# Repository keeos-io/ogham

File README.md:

# Ogham

A dual-voice **bytebeat synthesizer** for Eurorack, built on the Electro-Smith
Daisy Seed. This repository holds everything needed to build one: firmware
source, schematics, PCB, panel, and the fabrication package.

Instead of oscillators and wavetables, Ogham runs *bytebeat* expressions —
single lines of integer arithmetic that, evaluated over time, produce
surprisingly rich rhythmic and melodic patterns. It hosts a bank of them, plays
two at once, and clocks, pitches and modulates them from the rest of your rack.

- **Manual:** <https://keeos.io/docs/ogham-manual/> (or [`docs/ogham-manual.pdf`](docs/ogham-manual.pdf))
- **Firmware downloads and changelog:** <https://keeos.io/firmware/ogham/>
- **Module overview:** <https://keeos.io/modules/ogham/>

> **Status: prototype.** Built and tested on a handful of units, not qualified
> for production. Published so others can learn from it and build on it. Check
> the design yourself before you commit money to a fab run.

## What's here

| Path | Contents |
|---|---|
| [`firmware/`](firmware/) | Firmware source, build and flashing instructions |
| [`hardware/ogham-merged-v1.0/`](hardware/ogham-merged-v1.0/) | KiCad schematics and PCB — the shipping revision |
| [`hardware/panel/`](hardware/panel/) | Front panel: artwork, and the panel PCB project |
| [`hardware/production/`](hardware/production/) | Gerbers, BOM, placement — ready to upload to a fab |
| [`docs/`](docs/) | Build instructions, and the manual as a PDF |
| `lib/` | libDaisy and DaisySP, as pinned submodules |

Only the **current** board revision is published. Earlier prototypes are not
included, so there is nothing here to fabricate by mistake.

## Quick start

**To build the firmware** — [`docs/BUILDING.md`](docs/BUILDING.md) has the full
set-up for Windows, macOS and Linux; [`firmware/README.md`](firmware/README.md)
covers the firmware itself. In short:

```bash
git clone --recurse-submodules https://github.com/keeos-io/ogham.git
cd ogham && make -C lib/libDaisy -j8 && make -C lib/DaisySP -j8
cd firmware && make -j8
```

`--recurse-submodules` is not optional: libDaisy has nested submodules of its
own, and without them the build fails part-way with a missing HAL object.

**To have the boards made** — see [`hardware/README.md`](hardware/README.md).
Upload `hardware/production/ogham-merged-v1.0.zip`, and **read the
hand-populate list first**: several parts are deliberately excluded from
assembly and a board built from the BOM alone will be missing them.

## Licensing

Firmware is **MIT**. Hardware and documentation are **CC BY-SA 4.0**. Build one,
sell one, fork it — but share hardware modifications alike, and give credit. The
*Keeos* name and the panel identity are not covered.

Full terms in [`LICENSE.md`](LICENSE.md); third-party components and the panel
typefaces in [`THIRD-PARTY.md`](THIRD-PARTY.md).

## A note on reproducible builds

The published binaries are byte-for-byte reproducible from this repository.
Building the firmware at a given tag, with the submodules at their pinned
commits and **Arm GNU Toolchain 14.2.Rel1**, reproduces the exact `.bin` shipped
for that release — verified, not assumed.

Two things will break that: building against a *different* libDaisy commit, or a
different compiler version. Both produce working firmware; neither reproduces the
published checksums. If you are verifying a download rather than developing,
compare against the SHA-256 published with each release.

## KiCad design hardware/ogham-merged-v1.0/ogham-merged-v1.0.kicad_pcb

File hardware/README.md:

# Ogham hardware

KiCad 10 sources and a ready-to-upload fabrication package for the shipping
board revision, **ogham-merged-v1.0**.

| | |
|---|---|
| Main PCB | 50 × 110 mm, 2-layer, double-sided SMT |
| Panel | 10 HP (50.5 × 128.5 mm) |
| Depth behind panel | ~32 mm including power-cable clearance — skiff-friendly |
| Supply | Eurorack ±12 V; the Seed runs from +12 V through a series Schottky, and an on-board +5 V regulator feeds the display and logic |
| MCU | Electro-Smith Daisy Seed (STM32H750), on pin-header standoffs |

Only this revision is published. Earlier prototypes (`ogham-logic`, `ogham-ui`
and their v0.2 iterations) are not included, so there is nothing here to
fabricate by mistake.

## Layout

| Path | Contents |
|---|---|
| `ogham-merged-v1.0/` | Schematics (hierarchical: power, MCU, CV I/O, audio, UI), PCB, netlist |
| `panel/` | Panel artwork as SVG, and the panel as a fabricable PCB (`PanelPCB-v2/`) |
| `production/` | Gerbers, BOM, placement, IPC netlist, and the interactive BOM |

The schematic is a two-level hierarchy: `ogham-merged-v1.0` is the root, and it
pulls in `ogham-logic-v2.0` (→ power, MCU, CV I/O) and `ogham-ui-v0.2` (→ audio,
UI). Those two keep the sheet names they had when the design was two separate
boards — they are **not** old revisions, they are live sub-sheets of this one.

## 3D models are not included

The PCB references five third-party 3D models. They are other people's files, in
one case 34 MB of one, and several arrived without a licence attached, so they
are not redistributed here. Everything else the board needs is in this
repository; only the 3D viewer is affected, and the board fabricates,
assembles and works without them.

The references are `${KIPRJMOD}`-relative, which means KiCad resolves them
against the project directory. Create `hardware/_libs/` and drop the files in
at these paths and the 3D view fills in with no edit to the PCB:

| Path under `hardware/_libs/` | Part | Source | Licence |
|---|---|---|---|
| `AudioJacks/AudioJacks.3dshapes/PJ398SM_Hex_nut.step` | Thonkiconn PJ398SM jacks | [clacktronics/AudioJacks](https://github.com/clacktronics/AudioJacks) | MIT |
| `kicad-3dmodels/potentiometers/ALPHA-RD901F-40.step` | Alpha 9mm pots | [dhaillant/kicad-3dmodels](https://github.com/dhaillant/kicad-3dmodels) | GPL-3.0 |
| `TM1637/YAAJ_4_Digit_LED_Display_0_36_Dots_TM1637_PinHeader_Left_cp.step` | TM1637 display | [yet-another-average-joe/KiCad-Chinese_Modules](https://github.com/yet-another-average-joe/KiCad-Chinese_Modules) | not stated upstream |
| `DaisySeed/ES_Daisy_Seed_Rev7-1.step` | Daisy Seed | Electro-Smith | not stated on the copy used here |
| `Encoder/EC11E1834403/3D/EC11E1834403.stp` | EC11 encoder | manufacturer model; provenance not recorded | unknown |
| `vendor/2MS1T1B1M2QES--3DModel-STEP-56544.STEP` | Mode toggle switch | manufacturer model | unknown |
| `vendor/TAP106J016SCS.STEP` | Tantalum capacitor | manufacturer model | unknown |

A missing model is a warning, not an error: KiCad opens the board and reports
which ones it could not find. Note also that each jack footprint carries a
second, dead model entry naming `${KICAD9_3DMODEL_DIR}`, a KiCad 9 path
variable that KiCad 10 does not define. The jacks render from the AudioJacks
model above, so that entry can be ignored.

## Browse the design without installing anything

[KiCanvas](https://kicanvas.org) renders KiCad files in the browser, straight
from this repository — pan, zoom, click a symbol, follow a net. Nothing to
install, nothing to download.

| | |
|---|---|
| Schematic and PCB | [Open in KiCanvas](https://kicanvas.org/?github=https://github.com/keeos-io/ogham/tree/main/hardware/ogham-merged-v1.0) |
| Panel PCB | [Open in KiCanvas](https://kicanvas.org/?github=https://github.com/keeos-io/ogham/tree/main/hardware/panel/PanelPCB-v2) |

Both links point at a **directory**, not at a file, and that is deliberate. Given
a single `.kicad_sch` KiCanvas loads it alone, which for a hierarchical design
means the root sheet and nothing below it — you would get a page of sheet symbols
with no way into them. Pointed at the directory it enumerates every file, so all
nine sheets resolve and the board is in the same viewer, behind the file picker
at the top left.

This matters more than convenience: these are **KiCad 10** sources, and KiCad 9
cannot open them at all. Until you have KiCad 10 in front of you, the links above
are the only way to read the circuit.

KiCanvas is a third-party viewer and fetches from GitHub anonymously, so it is
subject to GitHub's rate limits and is nobody's idea of a permanent archive. The
files in this repository are the source of truth; the links are a convenience.

## Having the boards made

The package in `production/` is formatted for JLCPCB assembly, but the gerbers
are standard and will work anywhere. **Read
[`production/JLC-upload-checklist.md`](production/JLC-upload-checklist.md)
before ordering** — it covers the whole flow, including the two things most
likely to cost you a board run.

### ⚠ 1. Nineteen parts must be marked "Do Not Place"

90 SMD parts are machine-assembled. **19 designators across 13 BOM rows are
hand-soldered** and will be flagged by the fab as unresolvable, because they
carry no LCSC number. Mark every one of them DNP:

- **C5** — 10 µF tantalum (`TAP106J016SCS`). This one is easy to miss: it looks
  like an ordinary SMD part in the BOM and it is the **+5 V bulk capacitor**, so
  a board that quietly ships without it is not a board you want.
- **A1** — the Daisy Seed
- **J1** — Eurorack power header
- **8 × jacks** — `J_CLK1`, `J_CVA1`, `J_CVB1`, `J_GATE_IN1`, `J_CV_OUT1`,
  `J_GATE_OUT1`, `J_OUT1`, `J_OUT2`
- **J_DISP1**, **J_DISP_SUPP** — display headers
- **4 × pots** — `RVA1`, `RVB1`, `RVLEVEL1`, `RVRATE1`
- **SW_ENC1** — encoder · **SW_MODE1** — mode toggle

### ⚠ 2. Check rotations before you confirm

Rotation is the classic assembly error — KiCad and the fab disagree about
reference orientation. Step through the placement preview and check the
polarised parts: diode cathodes (D1, D2, D8, D3, D4, D5, D_OCT1, D_OCT2, D6,
D7), IC pin-1 (U1–U7), and Q1's collector/emitter. Assembly is **double-sided**,
so also confirm the top-layer parts really are on top.

## Interactive BOM — use this while assembling

[`production/ogham-merged-v1.0-ibom.html`](production/ogham-merged-v1.0-ibom.html)
is a single self-contained file: click a line in the BOM and those parts light up
on the board, front and back, with checkboxes for tracking what you have sourced
and placed. No install, no network — **download it and open it in a browser**.

> GitHub displays committed HTML as source rather than rendering it, so use the
> download button rather than clicking through — the file is useless as text and
> perfectly good once saved.

It carries an **LCSC** column, which doubles as the hand-populate list: a part
with an LCSC number is machine-assembled, and a part **without** one is yours to
solder. `C5` shows its bare MPN `TAP106J016SCS`, and the jacks, pots, encoder and
headers show nothing at all — those are exactly the 19 designators to mark Do Not
Place.

Regenerate it with [`gen-ibom.sh`](gen-ibom.sh) whenever the board changes; the
output is committed, so it can otherwise drift from the design. It needs KiCad's
own Python and [InteractiveHtmlBom](https://github.com/openscopeproject/InteractiveHtmlBom)
**v2.11.2 or newer** — earlier versions cannot read KiCad 10 files.

## Hand-populated parts

Sources that have worked (UK):

| Part | Qty | Where |
|---|---|---|
| Thonkiconn PJ398SM jacks | 8 | [thonk.co.uk](https://www.thonk.co.uk/shop/thonkiconn/) |
| Alpha 9 mm B10K D-shaft pots | 4 | [thonk.co.uk](https://www.thonk.co.uk/shop/alpha-9mm-pots-dshaft/) |
| Rotary encoder, Bourns `PEC11R-4115K-S0018` | 1 | Any distributor — Mouser, Farnell, Digi-Key |
| Breakaway pin header | 1 bag | [thonk.co.uk](https://www.thonk.co.uk/shop/60-pin-header/) |
| 2×5 IDC power header | 1 | Mouser / Soundtronics / York Modular |
| Daisy Seed (Rev 4) | 1 | Electro-Smith |
| C5, 10 µF tantalum | 1 | Any distributor — `TAP106J016SCS` or equivalent |

> **Encoder note.** `PEC11R-4115K-S0018` is a 15 mm knurled (T18) shaft with a
> push switch, 18 detents and 18 pulses per revolution — one pulse per detent.
> It is the swapped-A/B part, which the **default** firmware build targets. Two
> batches exist with opposite A/B phase and the firmware cannot tell them apart,
> so if the Func encoder counts down when turned clockwise, flash the other
> build — see [`../firmware/README.md`](../firmware/README.md).
>
> **Why the 15 mm shaft.** It matches the Alpha pots dimensionally: the same
> 5 mm M7 × 0.75 bushing and the same 15 mm from mounting shoulder to shaft tip,
> so the encoder knob sits level with the four pot knobs rather than standing
> proud of them. The 20 mm variant of the same encoder carries a 7 mm bushing
> and would not. The cost of that choice is a short thread — 5 mm of bushing
> against a 1.6 mm panel — so expect to pack a washer under the nut to pull the
> encoder flush.

## Panel

`panel/` holds the artwork as SVG and as a fabricable PCB, which is how the
panels were actually made — a PCB panel is cheap, flat, and takes the graphics as
silkscreen.

`Ogham Panel Graphics (JLCPCB) v2.svg` is the editable artwork, and
`PanelPCB-v2/` is the KiCad project converted from it — that project, and the
gerbers in its `production/`, are what the built modules use. The first
revision has been removed to leave only one panel to order from; it is still in
the git history if you want it.

**The fabrication files do not depend on any fonts.** The artwork is stored as
polygons, converted from the SVG, so a panel ordered from
`PanelPCB-v2/production/` comes out right regardless of what is installed on your
machine.

**Editing the SVG does need fonts**, though all three are now free and
redistributable — the v2 artwork replaced Bahnschrift, a Windows system font,
with DINish. See
[`../THIRD-PARTY.md`](../THIRD-PARTY.md) for the full list and what to do on
macOS or Linux.

## Design notes

`ogham_pins.h` in the firmware is the pin-assignment source of truth and matches
this schematic. If you rework the board, keep them in step.

Two constraints worth knowing before you move things: the TM1637 display sits on
**D9/D10 (PB4/PB5)**, which are SPI pins with **no I²C alternate function** — an
I²C peripheral needs different pins. Seed pins 12/13 (PB8/PB9, I²C1) are
unconnected and are the obvious place to go.

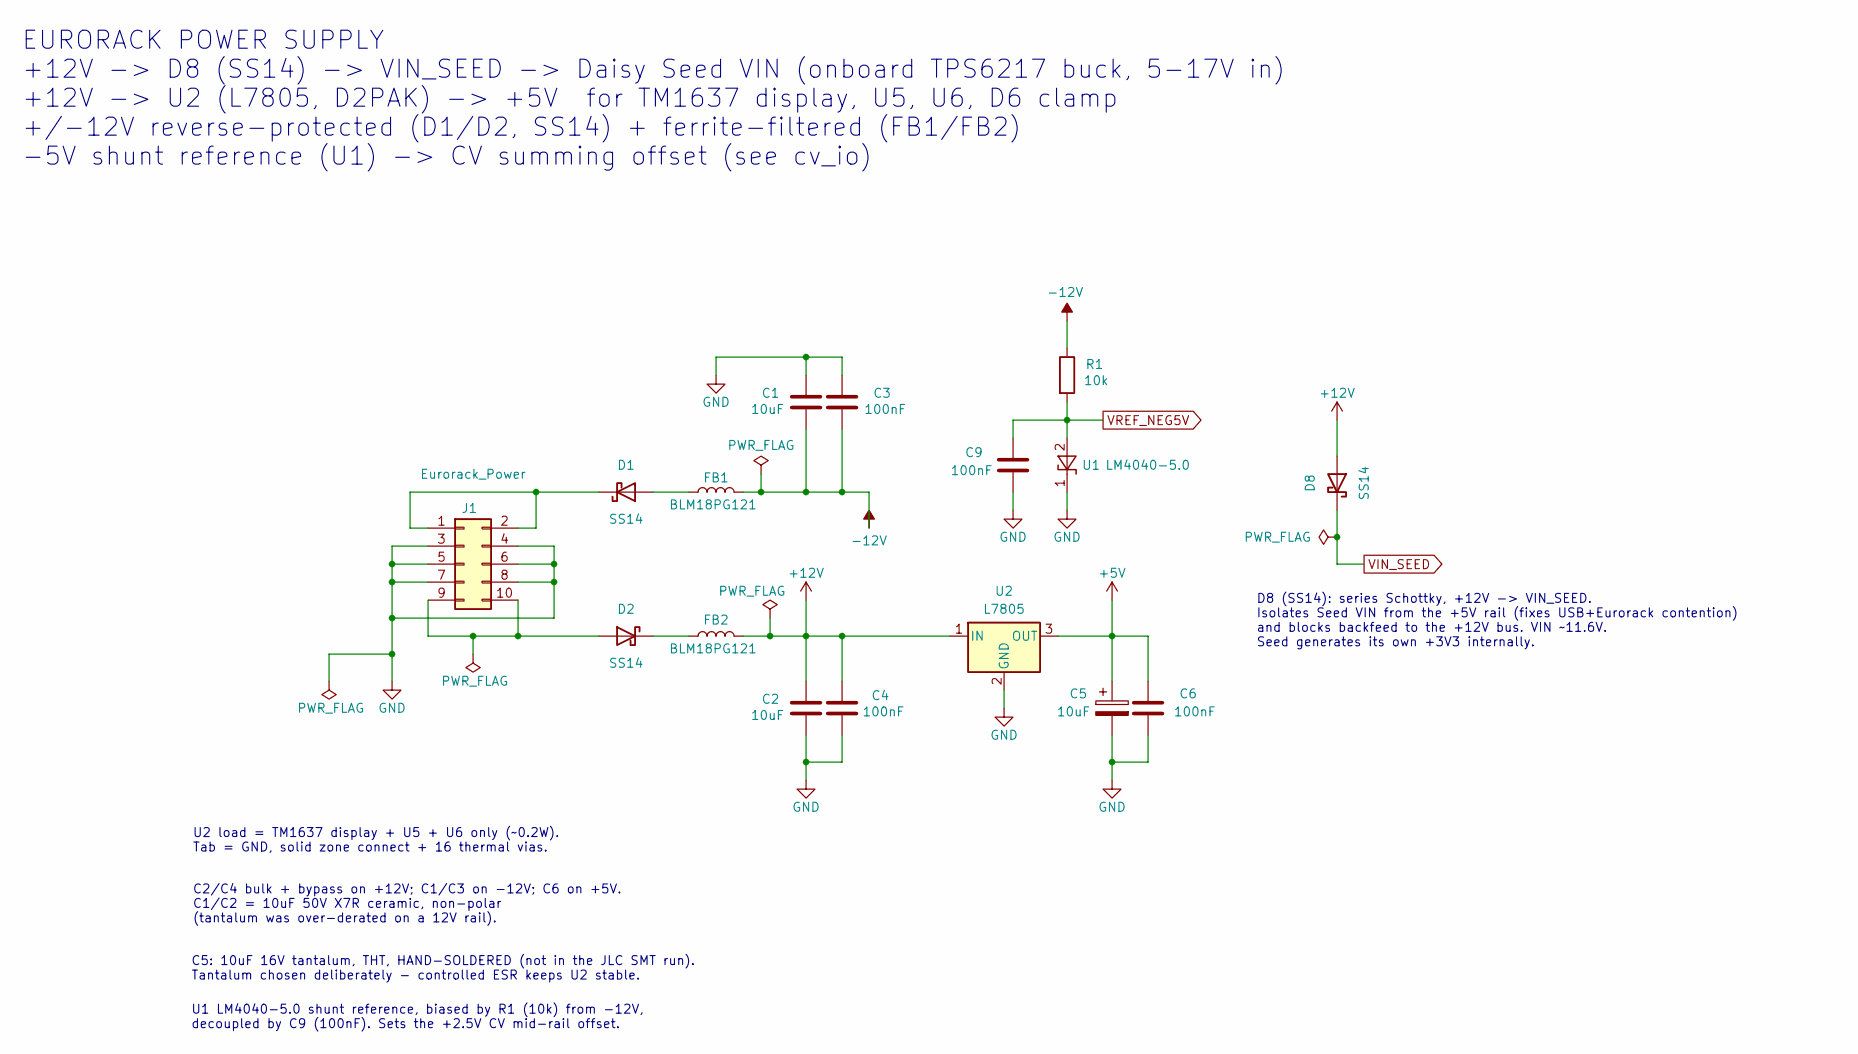
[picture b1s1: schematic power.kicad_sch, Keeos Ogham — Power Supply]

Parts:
C1, C2: 10uF; C_1210_3225Metric; LCSC C138687
C3, C4, C6, C9: 100nF; C_0603_1608Metric; LCSC C14663
C5: 10uF; CP_Radial_D5.0mm_P2.50mm; LCSC TAP106J016SCS
D1, D2, D8: SS14; D_SMA; LCSC C2480
FB1, FB2: BLM18PG121; L_0603_1608Metric; LCSC C14709
J1: Eurorack_Power; PinHeader_2x05_P2.54mm_Vertical
R1: 10k; R_0603_1608Metric; LCSC C25804
U1: LM4040-5.0; SOT-23; LCSC C156302
U2: L7805; TO-263-2; LCSC C15077

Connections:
+5V: C5.1, C6.1, U2.3 (OUT); also elsewhere on the board
+12V: C2.1, C4.1, D8.2 (A), FB2.2, U2.1 (IN); also elsewhere on the board
-12V: C1.2, C3.2, FB1.2, R1.1; also elsewhere on the board
GND: C1.1, C2.2, C3.1, C4.2, C5.2, C6.2, C9.2, J1.3, J1.4, J1.5, J1.6, J1.7, J1.8, U1.1 (K), U2.2 (GND); also elsewhere on the board
unnamed: D1.2 (A), FB1.1
unnamed: D1.1 (K), J1.1, J1.2
unnamed: D2.2 (A), J1.9, J1.10
unnamed: D2.1 (K), FB2.1
VIN_SEED: D8.1 (K); also elsewhere on the board
VREF_NEG5V: C9.1, R1.2, U1.2 (A); also elsewhere on the board

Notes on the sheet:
U1 LM4040-5.0 shunt reference, biased by R1 (10k) from -12V, decoupled by C9 (100nF). Sets the +2.5V CV mid-rail offset.
EURORACK POWER SUPPLY +12V -> D8 (SS14) -> VIN_SEED -> Daisy Seed VIN (onboard TPS6217 buck, 5-17V in) +12V -> U2 (L7805, D2PAK) -> +5V for TM1637 display, U5, U6, D6 clamp +/-12V reverse-protected (D1/D2, SS14) + ferrite-filtered (FB1/FB2) -5V shunt reference (U1) -> CV summing offset (see cv_io)
D8 (SS14): series Schottky, +12V -> VIN_SEED. Isolates Seed VIN from the +5V rail (fixes USB+Eurorack contention) and blocks backfeed to the +12V bus. VIN ~11.6V. Seed generates its own +3V3 internally.
C5: 10uF 16V tantalum, THT, HAND-SOLDERED (not in the JLC SMT run). Tantalum chosen deliberately - controlled ESR keeps U2 stable.
U2 load = TM1637 display + U5 + U6 only (~0.2W). Tab = GND, solid zone connect + 16 thermal vias.
C2/C4 bulk + bypass on +12V; C1/C3 on -12V; C6 on +5V. C1/C2 = 10uF 50V X7R ceramic, non-polar (tantalum was over-derated on a 12V rail).

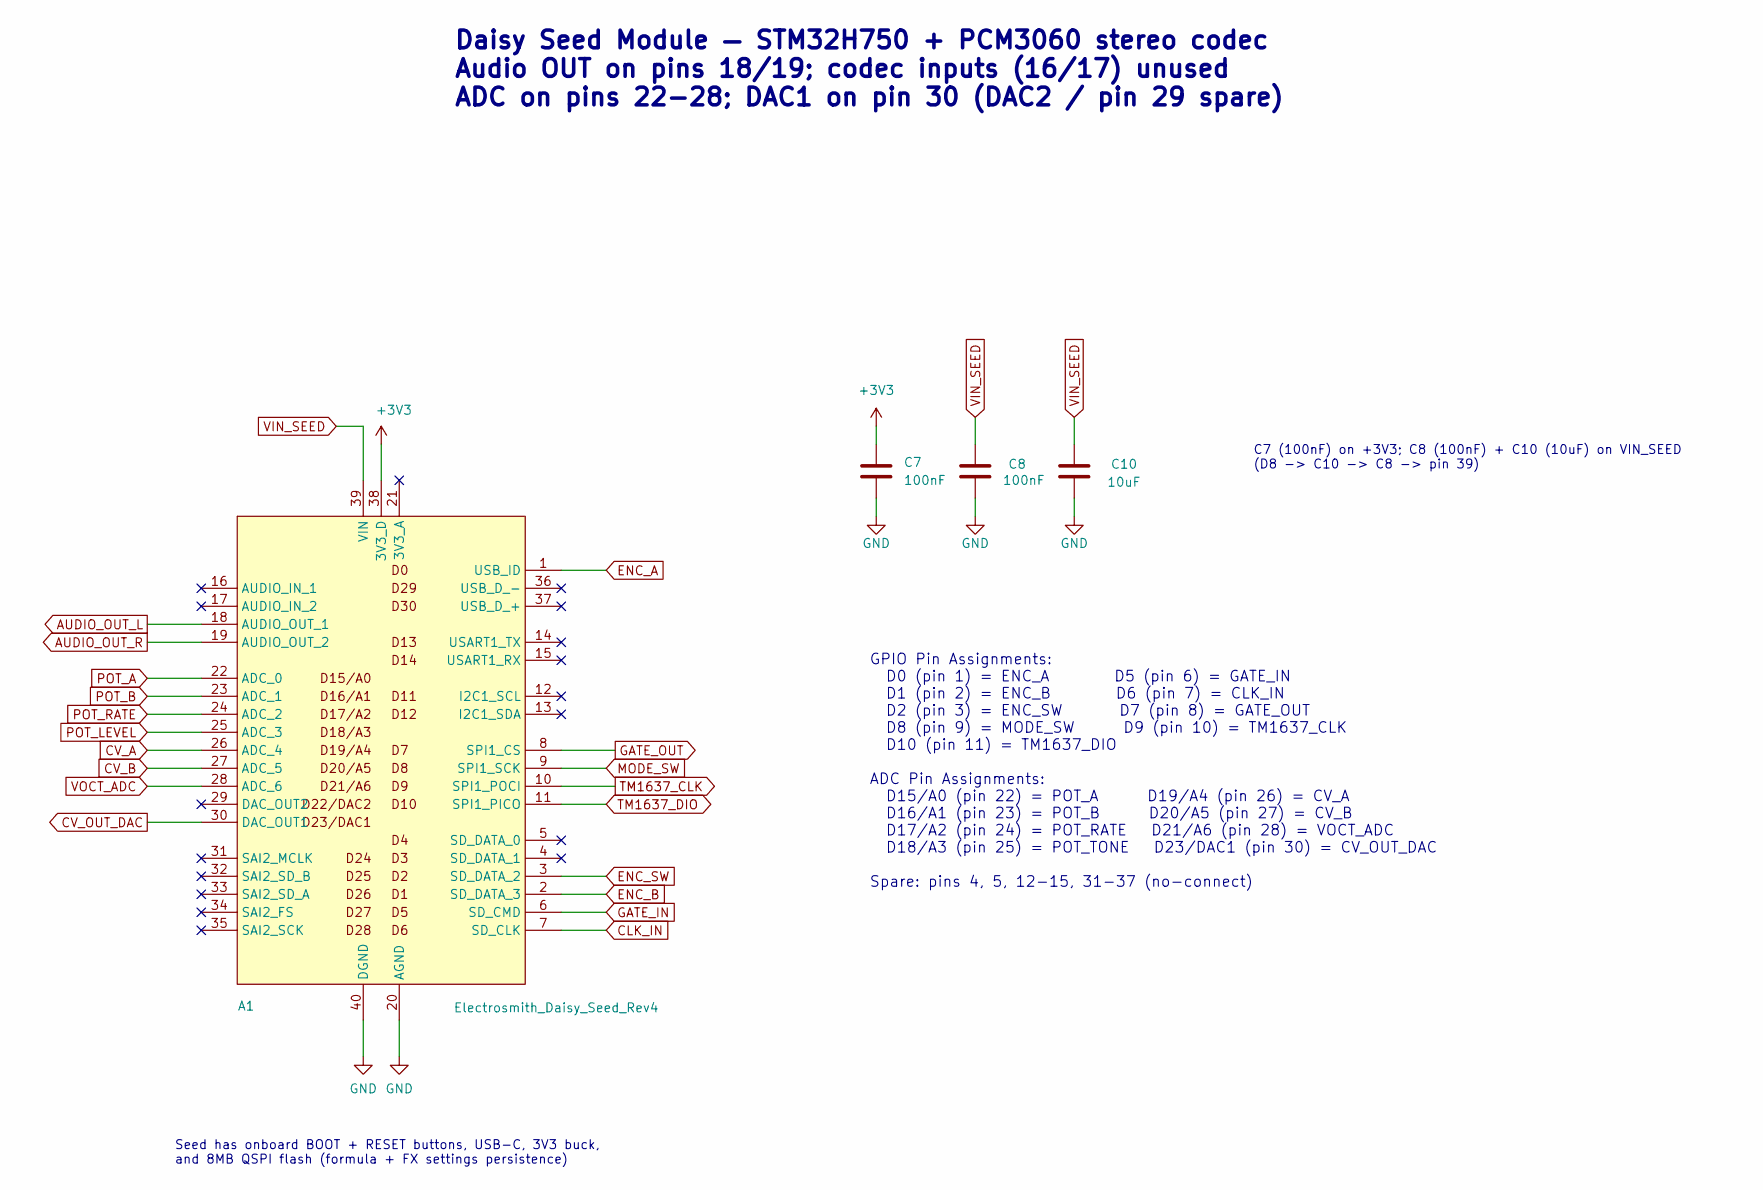
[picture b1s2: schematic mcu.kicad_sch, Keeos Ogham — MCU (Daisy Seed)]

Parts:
A1: Electrosmith_Daisy_Seed_Rev4; Electrosmith_Daisy_Seed
C7, C8: 100nF; C_0603_1608Metric; LCSC C14663
C10: 10uF; C_1210_3225Metric; LCSC C138687

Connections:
+3V3: A1.38 (3V3_D), C7.1; also elsewhere on the board
AUDIO_OUT_L: A1.18 (AUDIO_OUT_1); also elsewhere on the board
AUDIO_OUT_R: A1.19 (AUDIO_OUT_2); also elsewhere on the board
CLK_IN: A1.7 (SD_CLK); also elsewhere on the board
CV_A: A1.26 (ADC_4); also elsewhere on the board
CV_B: A1.27 (ADC_5); also elsewhere on the board
CV_OUT_DAC: A1.30 (DAC_OUT1); also elsewhere on the board
ENC_A: A1.1 (USB_ID); also elsewhere on the board
ENC_B: A1.2 (SD_DATA_3); also elsewhere on the board
ENC_SW: A1.3 (SD_DATA_2); also elsewhere on the board
GATE_IN: A1.6 (SD_CMD); also elsewhere on the board
GATE_OUT: A1.8 (SPI1_CS); also elsewhere on the board
GND: A1.20 (AGND), A1.40 (DGND), C7.2, C8.2, C10.2; also elsewhere on the board
MODE_SW: A1.9 (SPI1_SCK); also elsewhere on the board
POT_A: A1.22 (ADC_0); also elsewhere on the board
POT_B: A1.23 (ADC_1); also elsewhere on the board
POT_LEVEL: A1.25 (ADC_3); also elsewhere on the board
POT_RATE: A1.24 (ADC_2); also elsewhere on the board
TM1637_CLK: A1.10 (SPI1_POCI); also elsewhere on the board
TM1637_DIO: A1.11 (SPI1_PICO); also elsewhere on the board
VIN_SEED: A1.39 (VIN), C8.1, C10.1; also elsewhere on the board
VOCT_ADC: A1.28 (ADC_6); also elsewhere on the board

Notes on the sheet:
C7 (100nF) on +3V3; C8 (100nF) + C10 (10uF) on VIN_SEED (D8 -> C10 -> C8 -> pin 39)
Daisy Seed Module — STM32H750 + PCM3060 stereo codec Audio OUT on pins 18/19; codec inputs (16/17) unused ADC on pins 22-28; DAC1 on pin 30 (DAC2 / pin 29 spare)
GPIO Pin Assignments: D0 (pin 1) = ENC_A D5 (pin 6) = GATE_IN D1 (pin 2) = ENC_B D6 (pin 7) = CLK_IN D2 (pin 3) = ENC_SW D7 (pin 8) = GATE_OUT D8 (pin 9) = MODE_SW D9 (pin 10) = TM1637_CLK D10 (pin 11) = TM1637_DIO ADC Pin Assignments: D15/A0 (pin 22) = POT_A D19/A4 (pin 26) = CV_A D16/A1 (pin 23) 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
Seed has onboard BOOT + RESET buttons, USB-C, 3V3 buck, and 8MB QSPI flash (formula + FX settings persistence)

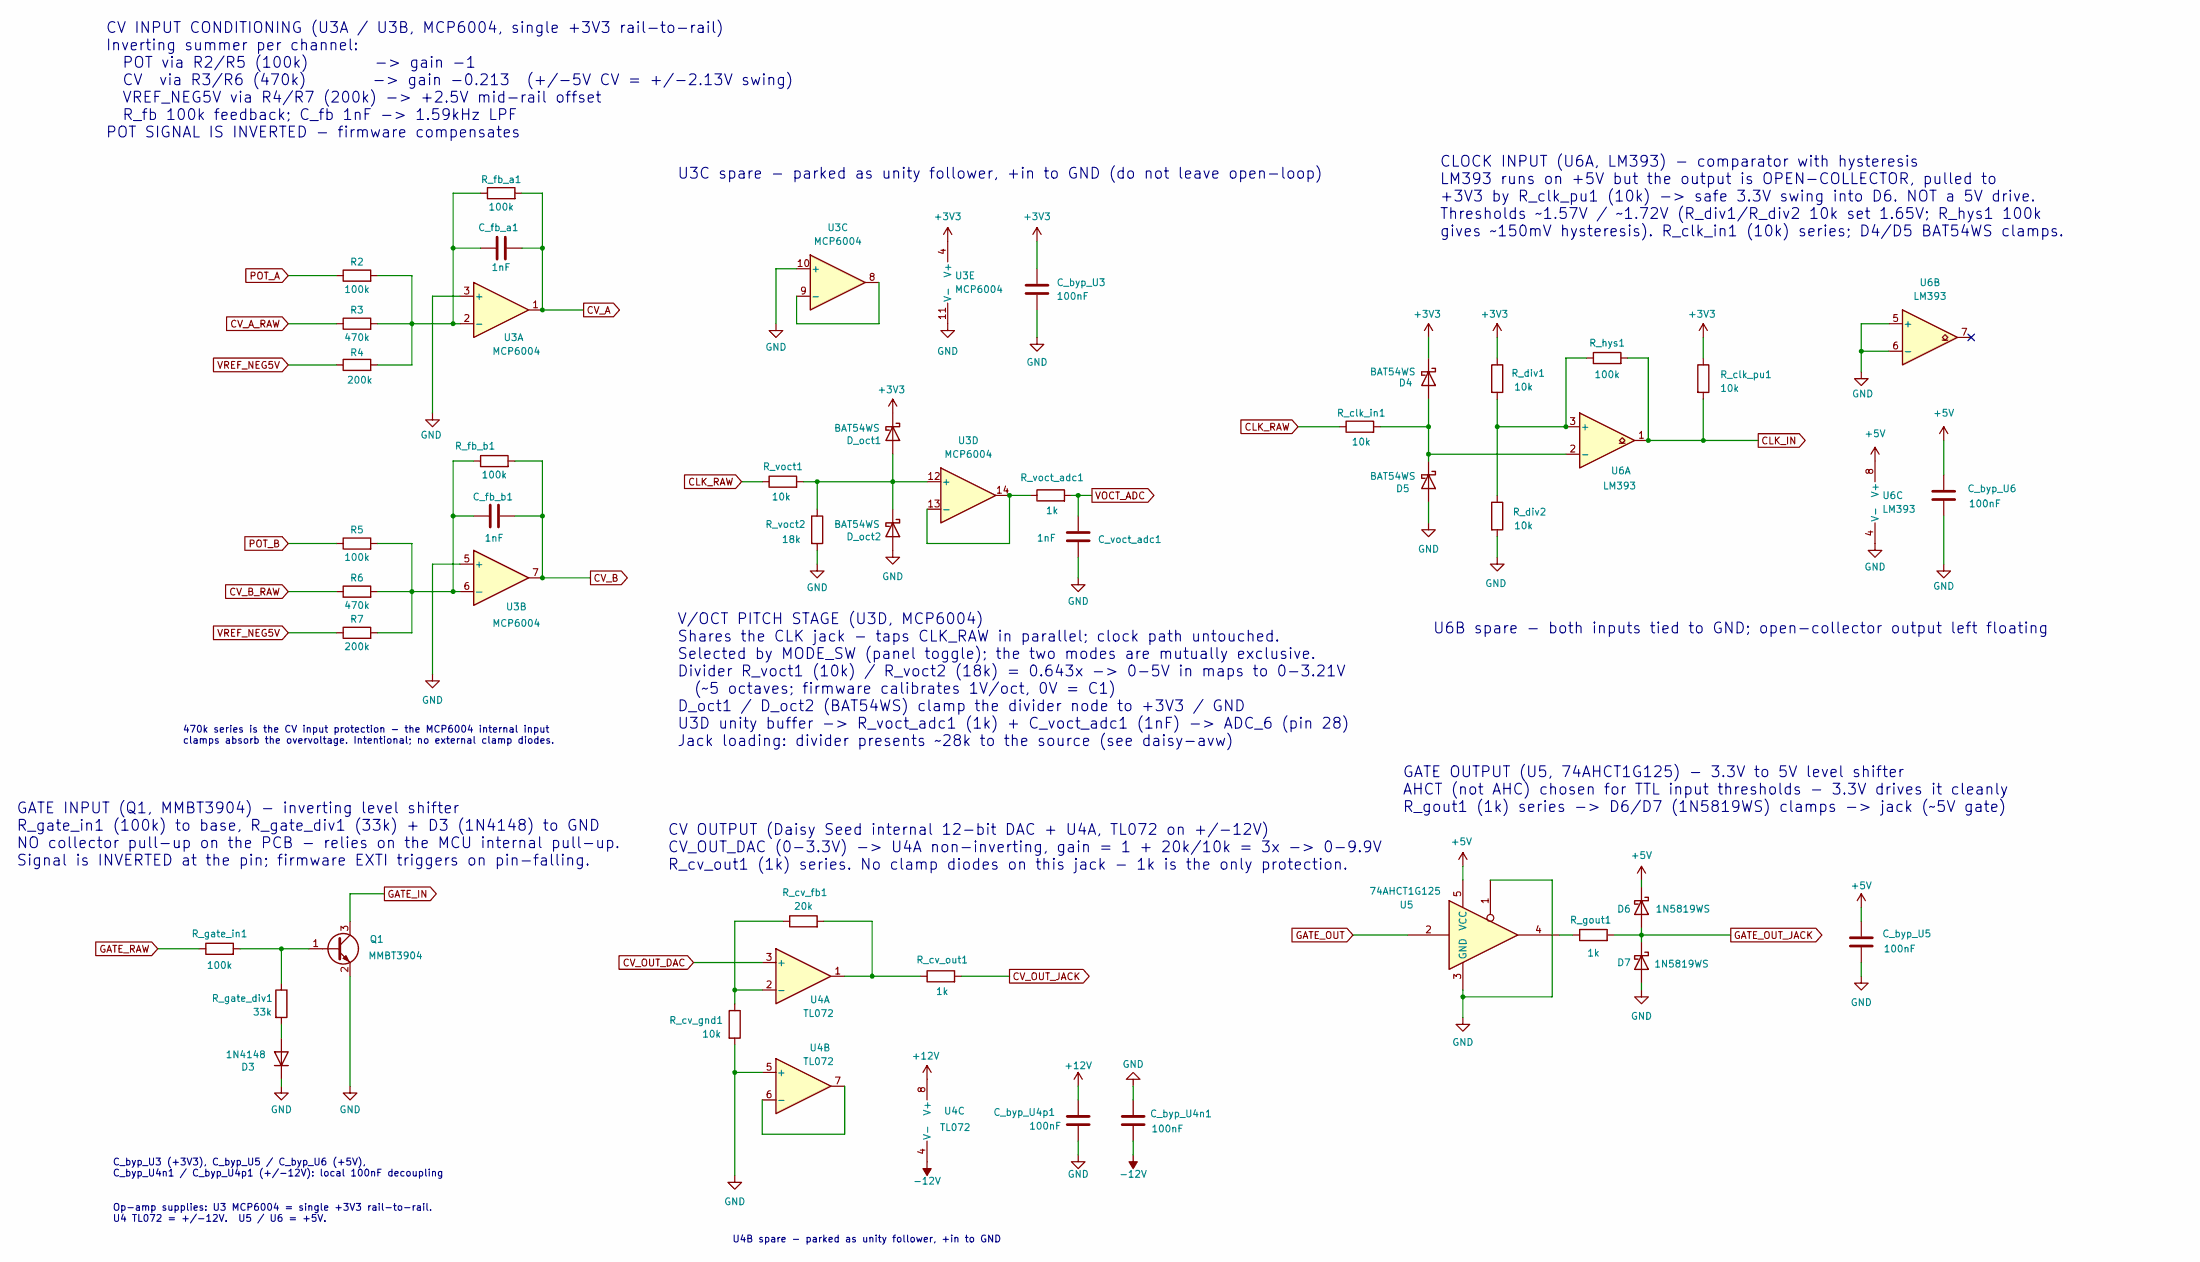
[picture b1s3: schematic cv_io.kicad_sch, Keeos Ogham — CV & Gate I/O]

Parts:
C_byp_U3, C_byp_U4n1, C_byp_U4p1, C_byp_U5, C_byp_U6: 100nF; C_0603_1608Metric; LCSC C14663
C_fb_a1: 1nF; C_0603_1608Metric; LCSC C1588
C_fb_b1: 1nF; C_0603_1608Metric; LCSC C1588
C_voct_adc1: 1nF; C_0603_1608Metric; LCSC C1588
D3: 1N4148; D_SOD-323; LCSC C2128
D4, D5: BAT54WS; D_SOD-323; LCSC C22629
D6, D7: 1N5819WS; D_SOD-323; LCSC C191023
D_oct1, D_oct2: BAT54WS; D_SOD-323; LCSC C22629
Q1: MMBT3904; SOT-23; LCSC C20526
R2, R5: 100k; R_0603_1608Metric; LCSC C25803
R3, R6: 470k; R_0603_1608Metric; LCSC C23178
R4, R7: 200k; R_0603_1608Metric; LCSC C25811
R_clk_in1: 10k; R_0603_1608Metric; LCSC C25804
R_clk_pu1: 10k; R_0603_1608Metric; LCSC C25804
R_cv_fb1: 20k; R_0603_1608Metric; LCSC C4184
R_cv_gnd1: 10k; R_0603_1608Metric; LCSC C25804
R_cv_out1: 1k; R_0603_1608Metric; LCSC C21190
R_div1, R_div2: 10k; R_0603_1608Metric; LCSC C25804
R_fb_a1: 100k; R_0603_1608Metric; LCSC C25803
R_fb_b1: 100k; R_0603_1608Metric; LCSC C25803
R_gate_div1: 33k; R_0603_1608Metric; LCSC C4216
R_gate_in1: 100k; R_0603_1608Metric; LCSC C25803
R_gout1: 1k; R_0603_1608Metric; LCSC C21190
R_hys1: 100k; R_0603_1608Metric; LCSC C25803
R_voct1: 10k; R_0603_1608Metric; LCSC C25804
R_voct2: 18k; R_0603_1608Metric; LCSC C25810
R_voct_adc1: 1k; R_0603_1608Metric; LCSC C21190
U3: MCP6004; TSSOP-14_4.4x5mm_P0.65mm; LCSC C50282
U4: TL072; SOIC-8_3.9x4.9mm_P1.27mm; LCSC C67473
U5: 74AHCT1G125; SOT-23-5; LCSC C7484
U6: LM393; SOIC-8_3.9x4.9mm_P1.27mm; LCSC C136033

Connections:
+3V3: C_byp_U3.1, D4.1 (K), D_oct1.1 (K), R_clk_pu1.1, R_div1.1, U3.4 (V+); also elsewhere on the board
+5V: C_byp_U5.1, C_byp_U6.1, D6.1 (K), U5.5 (VCC), U6.8 (V+); also elsewhere on the board
+12V: C_byp_U4p1.1, U4.8 (V+); also elsewhere on the board
-12V: C_byp_U4n1.2, U4.4 (V-); also elsewhere on the board
CLK_IN: R_clk_pu1.2, R_hys1.2, U6.1; also elsewhere on the board
CLK_RAW: R_clk_in1.1, R_voct1.1; also elsewhere on the board
CV_A: C_fb_a1.2, R_fb_a1.2, U3.1; also elsewhere on the board
CV_A_RAW: R3.1; also elsewhere on the board
CV_B: C_fb_b1.2, R_fb_b1.2, U3.7; also elsewhere on the board
CV_B_RAW: R6.1; also elsewhere on the board
CV_OUT_DAC: U4.3 (+); also elsewhere on the board
CV_OUT_JACK: R_cv_out1.2; also elsewhere on the board
GATE_IN: Q1.3 (C); also elsewhere on the board
GATE_OUT: U5.2; also elsewhere on the board
GATE_OUT_JACK: D6.2 (A), D7.1 (K), R_gout1.2; also elsewhere on the board
GATE_RAW: R_gate_in1.1; also elsewhere on the board
GND: C_byp_U3.2, C_byp_U4n1.1, C_byp_U4p1.2, C_byp_U5.2, C_byp_U6.2, C_voct_adc1.1, D3.1 (K), D5.2 (A), D7.2 (A), D_oct2.2 (A), Q1.2 (E), R_cv_gnd1.2, R_div2.2, R_voct2.2, U3.3 (+), U3.5 (+), U3.10 (+), U3.11 (V-), U4.5 (+), U5.1, U5.3 (GND), U6.4 (V-), U6.5 (+), U6.6 (-); also elsewhere on the board
unnamed: D3.2 (A), R_gate_div1.2
unnamed: D4.2 (A), D5.1 (K), R_clk_in1.2, U6.2 (-)
unnamed: D_oct1.2 (A), D_oct2.1 (K), R_voct1.2, R_voct2.1, U3.12 (+)
unnamed: Q1.1 (B), R_gate_div1.1, R_gate_in1.2
unnamed: R_cv_fb1.2, R_cv_out1.1, U4.1
unnamed: R_gout1.1, U5.4
unnamed: C_fb_a1.1, R2.2, R3.2, R4.2, R_fb_a1.1, U3.2 (-)
unnamed: C_fb_b1.1, R5.2, R6.2, R7.2, R_fb_b1.1, U3.6 (-)
unnamed: U3.8, U3.9 (-)
unnamed: R_voct_adc1.1, U3.13 (-), U3.14
unnamed: R_cv_fb1.1, R_cv_gnd1.1, U4.2 (-)
unnamed: U4.6 (-), U4.7
unnamed: R_div1.2, R_div2.1, R_hys1.1, U6.3 (+)
POT_A: R2.1; also elsewhere on the board
POT_B: R5.1; also elsewhere on the board
VOCT_ADC: C_voct_adc1.2, R_voct_adc1.2; also elsewhere on the board
VREF_NEG5V: R4.1, R7.1; also elsewhere on the board

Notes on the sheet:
U3C spare - parked as unity follower, +in to GND (do not leave open-loop)
U6B spare - both inputs tied to GND; open-collector output left floating
470k series is the CV input protection - the MCP6004 internal input clamps absorb the overvoltage. Intentional; no external clamp diodes.
V/OCT PITCH STAGE (U3D, MCP6004) Shares the CLK jack - taps CLK_RAW in parallel; clock path untouched. Selected by MODE_SW (panel toggle); the two modes are mutually exclusive. Divider R_voct1 (10k) / R_voct2 (18k) = 0.643x -> 0-5V in maps to 0-3.21V (~5 octaves; firmware calibrates 1V/oct, 0V = C1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
C_byp_U3 (+3V3), C_byp_U5 / C_byp_U6 (+5V), C_byp_U4n1 / C_byp_U4p1 (+/-12V): local 100nF decoupling
U4B spare - parked as unity follower, +in to GND
Op-amp supplies: U3 MCP6004 = single +3V3 rail-to-rail. U4 TL072 = +/-12V. U5 / U6 = +5V.
CV INPUT CONDITIONING (U3A / U3B, MCP6004, single +3V3 rail-to-rail) Inverting summer per channel: POT via R2/R5 (100k) -> gain -1 CV via R3/R6 (470k) -> gain -0.213 (+/-5V CV = +/-2.13V swing) VREF_NEG5V via R4/R7 (200k) -> +2.5V mid-rail offset R_fb 100k feedback; C_fb 1nF -> 1.59kHz LPF POT SIGN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
CLOCK INPUT (U6A, LM393) - comparator with hysteresis LM393 runs on +5V but the output is OPEN-COLLECTOR, pulled to +3V3 by R_clk_pu1 (10k) -> safe 3.3V swing into D6. NOT a 5V drive. Thresholds ~1.57V / ~1.72V (R_div1/R_div2 10k set 1.65V; R_hys1 100k gives ~150mV hysteresis). R_clk_in1 (10k) seri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
GATE INPUT (Q1, MMBT3904) - inverting level shifter R_gate_in1 (100k) to base, R_gate_div1 (33k) + D3 (1N4148) to GND NO collector pull-up on the PCB - relies on the MCU internal pull-up. Signal is INVERTED at the pin; firmware EXTI triggers on pin-falling.
GATE OUTPUT (U5, 74AHCT1G125) - 3.3V to 5V level shifter AHCT (not AHC) chosen for TTL input thresholds - 3.3V drives it cleanly R_gout1 (1k) series -> D6/D7 (1N5819WS) clamps -> jack (~5V gate)
CV OUTPUT (Daisy Seed internal 12-bit DAC + U4A, TL072 on +/-12V) CV_OUT_DAC (0-3.3V) -> U4A non-inverting, gain = 1 + 20k/10k = 3x -> 0-9.9V R_cv_out1 (1k) series. No clamp diodes on this jack - 1k is the only protection.

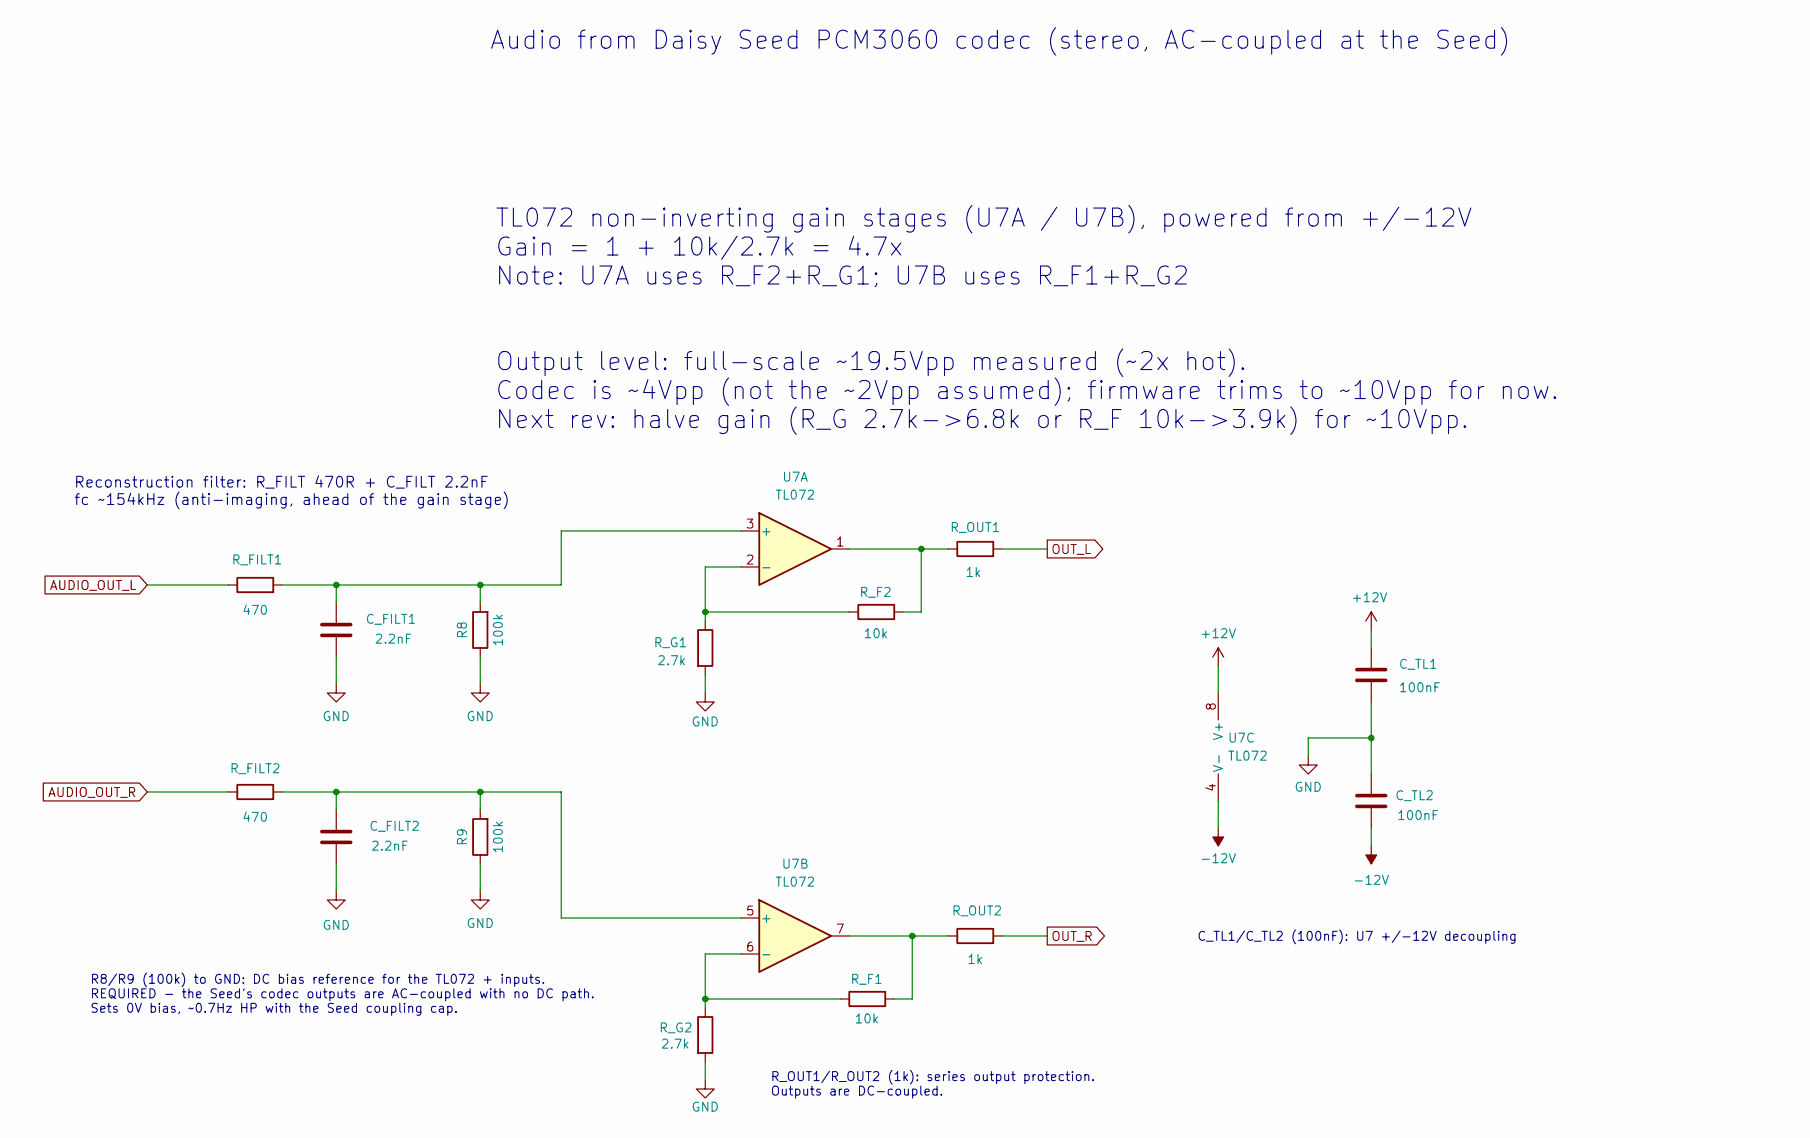
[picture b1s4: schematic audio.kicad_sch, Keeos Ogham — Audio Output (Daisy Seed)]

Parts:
C_FILT1, C_FILT2: 2.2nF; C_0603_1608Metric; LCSC C1604
C_TL1, C_TL2: 100nF; C_0603_1608Metric; LCSC C14663
R8, R9: 100k; R_0603_1608Metric; LCSC C25803
R_F1, R_F2: 10k; R_0603_1608Metric; LCSC C25804
R_FILT1, R_FILT2: 470; R_0603_1608Metric; LCSC C23179
R_G1, R_G2: 2.7k; R_0603_1608Metric; LCSC C13167
R_OUT1, R_OUT2: 1k; R_0603_1608Metric; LCSC C21190
U7: TL072; SOIC-8_3.9x4.9mm_P1.27mm; LCSC C67473

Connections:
+12V: C_TL1.1, U7.8 (V+); also elsewhere on the board
-12V: C_TL2.2, U7.4 (V-); also elsewhere on the board
AUDIO_OUT_L: R_FILT1.1; also elsewhere on the board
AUDIO_OUT_R: R_FILT2.1; also elsewhere on the board
GND: C_FILT1.2, C_FILT2.2, C_TL1.2, C_TL2.1, R8.1, R9.1, R_G1.2, R_G2.2; also elsewhere on the board
unnamed: R_F1.2, R_OUT2.1, U7.7
unnamed: R_F2.2, R_OUT1.1, U7.1
unnamed: C_FILT1.1, R8.2, R_FILT1.2, U7.3 (+)
unnamed: R_F2.1, R_G1.1, U7.2 (-)
unnamed: C_FILT2.1, R9.2, R_FILT2.2, U7.5 (+)
unnamed: R_F1.1, R_G2.1, U7.6 (-)
OUT_L: R_OUT1.2; also elsewhere on the board
OUT_R: R_OUT2.2; also elsewhere on the board

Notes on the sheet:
R_OUT1/R_OUT2 (1k): series output protection. Outputs are DC-coupled.
Audio from Daisy Seed PCM3060 codec (stereo, AC-coupled at the Seed)
TL072 non-inverting gain stages (U7A / U7B), powered from +/-12V Gain = 1 + 10k/2.7k = 4.7x Note: U7A uses R_F2+R_G1; U7B uses R_F1+R_G2
Output level: full-scale ~19.5Vpp measured (~2x hot). Codec is ~4Vpp (not the ~2Vpp assumed); firmware trims to ~10Vpp for now. Next rev: halve gain (R_G 2.7k->6.8k or R_F 10k->3.9k) for ~10Vpp.
Reconstruction filter: R_FILT 470R + C_FILT 2.2nF fc ~154kHz (anti-imaging, ahead of the gain stage)
R8/R9 (100k) to GND: DC bias reference for the TL072 + inputs. REQUIRED - the Seed's codec outputs are AC-coupled with no DC path. Sets 0V bias, ~0.7Hz HP with the Seed coupling cap.
C_TL1/C_TL2 (100nF): U7 +/-12V decoupling

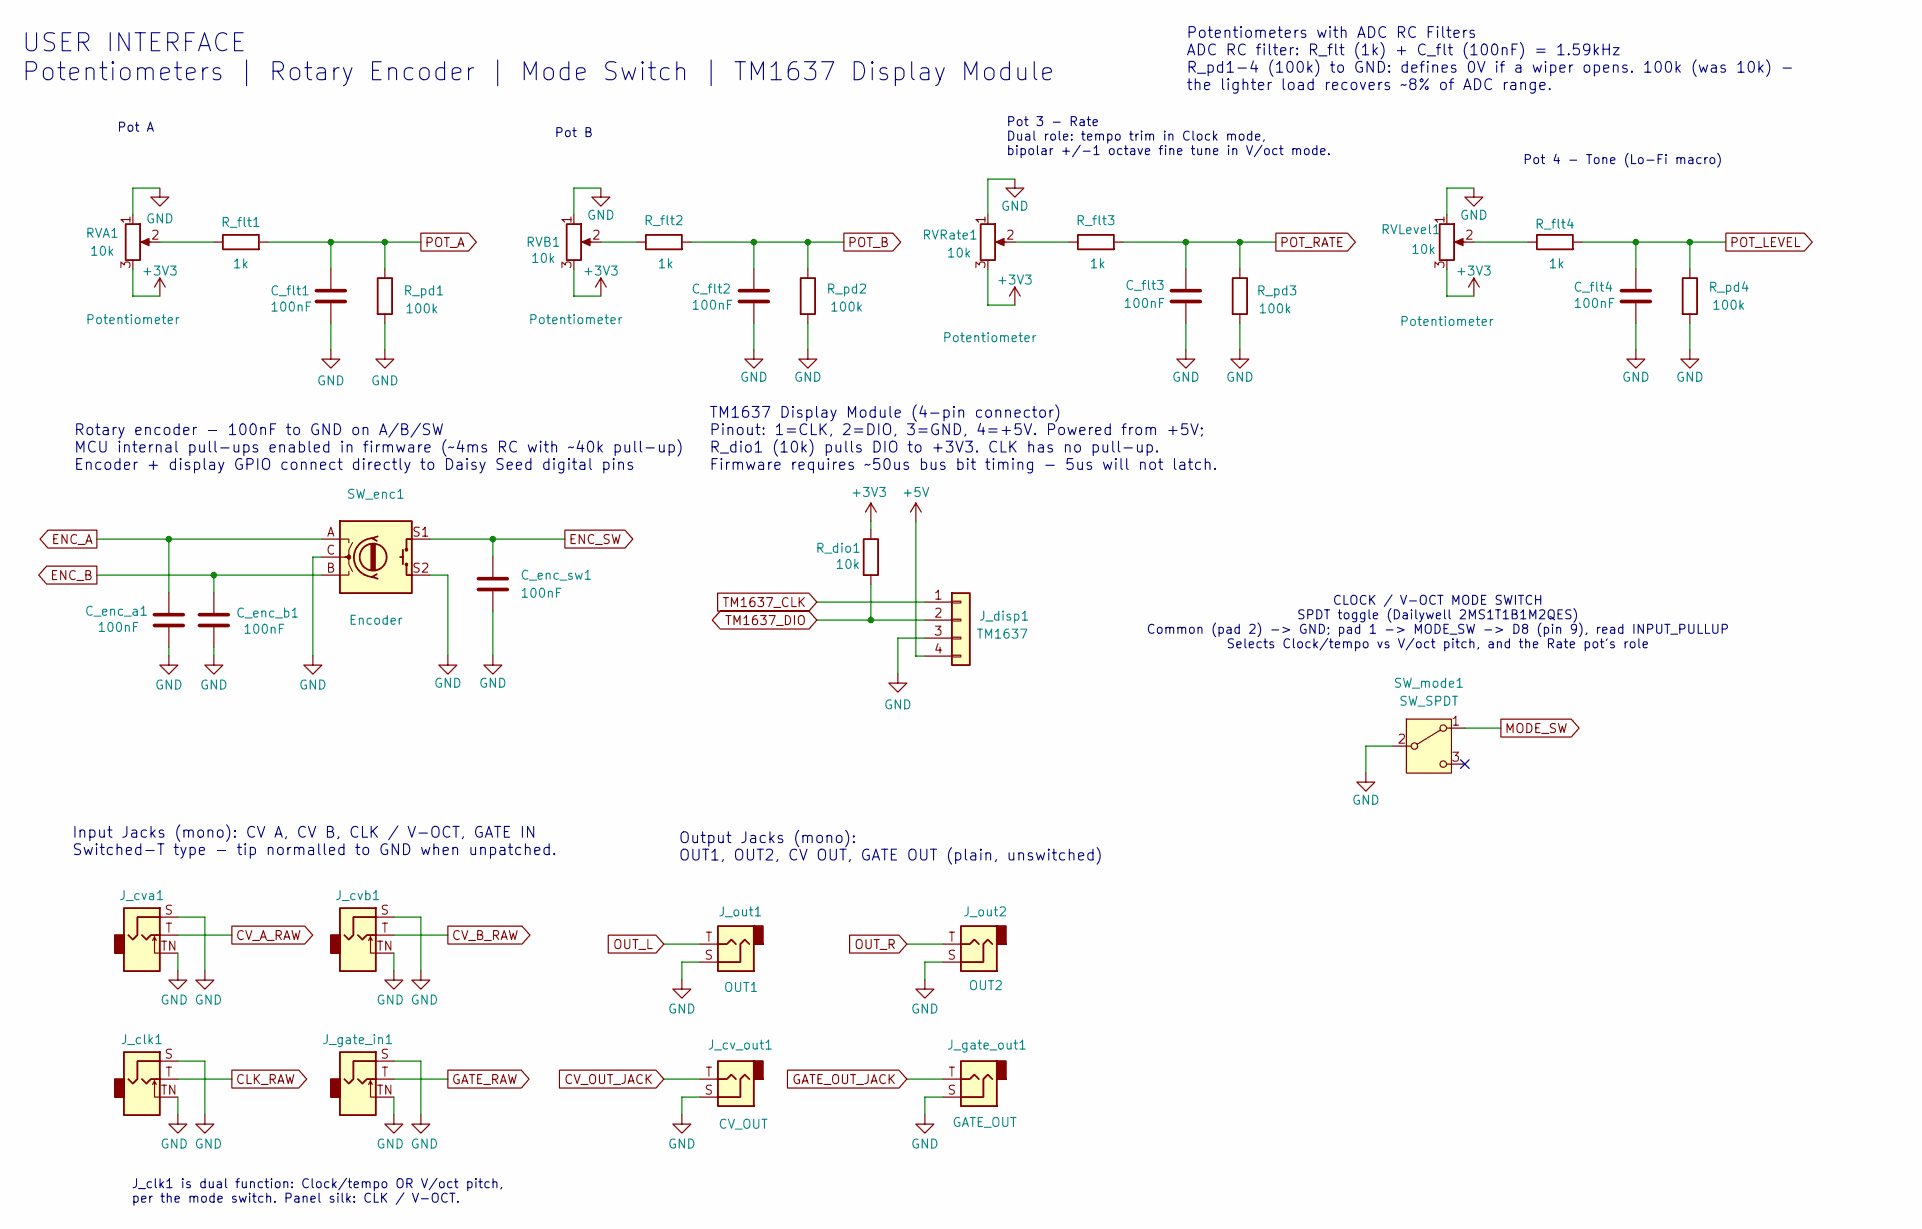
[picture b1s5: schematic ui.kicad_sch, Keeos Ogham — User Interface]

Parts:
C_enc_a1: 100nF; C_0603_1608Metric; LCSC C14663
C_enc_b1: 100nF; C_0603_1608Metric; LCSC C14663
C_enc_sw1: 100nF; C_0603_1608Metric; LCSC C14663
C_flt1, C_flt2, C_flt3, C_flt4: 100nF; C_0603_1608Metric; LCSC C14663
J_clk1: AudioJack2_SwitchT; Jack_3.5mm_QingPu_WQP-PJ398SM_Vertical_CircularHoles
J_cv_out1: CV_OUT; Jack_3.5mm_QingPu_WQP-PJ398SM_Vertical_CircularHoles
J_cva1: AudioJack2_SwitchT; Jack_3.5mm_QingPu_WQP-PJ398SM_Vertical_CircularHoles
J_cvb1: AudioJack2_SwitchT; Jack_3.5mm_QingPu_WQP-PJ398SM_Vertical_CircularHoles
J_disp1: TM1637; PinHeader_1x04_P2.54mm_Vertical
J_gate_in1: AudioJack2_SwitchT; Jack_3.5mm_QingPu_WQP-PJ398SM_Vertical_CircularHoles
J_gate_out1: GATE_OUT; Jack_3.5mm_QingPu_WQP-PJ398SM_Vertical_CircularHoles
J_out1: OUT1; Jack_3.5mm_QingPu_WQP-PJ398SM_Vertical_CircularHoles
J_out2: OUT2; Jack_3.5mm_QingPu_WQP-PJ398SM_Vertical_CircularHoles
RVA1: 10k; Potentiometer_Alpha_RD901F-40-00D_Single_Vertical
RVB1: 10k; Potentiometer_Alpha_RD901F-40-00D_Single_Vertical
RVLevel1: 10k; Potentiometer_Alpha_RD901F-40-00D_Single_Vertical
RVRate1: 10k; Potentiometer_Alpha_RD901F-40-00D_Single_Vertical
R_dio1: 10k; R_0603_1608Metric; LCSC C25804
R_flt1, R_flt2, R_flt3, R_flt4: 1k; R_0603_1608Metric; LCSC C21190
R_pd1, R_pd2, R_pd3, R_pd4: 100k; R_0603_1608Metric; LCSC C25803
SW_enc1: Encoder; RotaryEncoder_Alps_EC11E-Switch_Vertical_H20mm
SW_mode1: SW_SPDT; SW_2MS1T1B1M2QES

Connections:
+3V3: RVA1.3, RVB1.3, RVLevel1.3, RVRate1.3, R_dio1.1; also elsewhere on the board
+5V: J_disp1.4; also elsewhere on the board
CLK_RAW: J_clk1.T; also elsewhere on the board
CV_A_RAW: J_cva1.T; also elsewhere on the board
CV_B_RAW: J_cvb1.T; also elsewhere on the board
CV_OUT_JACK: J_cv_out1.T; also elsewhere on the board
ENC_A: C_enc_a1.1, SW_enc1.A; also elsewhere on the board
ENC_B: C_enc_b1.1, SW_enc1.B; also elsewhere on the board
ENC_SW: C_enc_sw1.1, SW_enc1.S1; also elsewhere on the board
GATE_OUT_JACK: J_gate_out1.T; also elsewhere on the board
GATE_RAW: J_gate_in1.T; also elsewhere on the board
GND: C_enc_a1.2, C_enc_b1.2, C_enc_sw1.2, C_flt1.2, C_flt2.2, C_flt3.2, C_flt4.2, J_clk1.S, J_clk1.TN, J_cv_out1.S, J_cva1.S, J_cva1.TN, J_cvb1.S, J_cvb1.TN, J_disp1.3, J_gate_in1.S, J_gate_in1.TN, J_gate_out1.S, J_out1.S, J_out2.S, RVA1.1, RVB1.1, RVLevel1.1, RVRate1.1, R_pd1.2, R_pd2.2, R_pd3.2, R_pd4.2, SW_enc1.C, SW_enc1.S2, SW_mode1.2 (B); also elsewhere on the board
MODE_SW: SW_mode1.1 (A); also elsewhere on the board
unnamed: RVA1.2, R_flt1.1
unnamed: RVB1.2, R_flt2.1
unnamed: RVLevel1.2, R_flt4.1
unnamed: RVRate1.2, R_flt3.1
OUT_L: J_out1.T; also elsewhere on the board
OUT_R: J_out2.T; also elsewhere on the board
POT_A: C_flt1.1, R_flt1.2, R_pd1.1; also elsewhere on the board
POT_B: C_flt2.1, R_flt2.2, R_pd2.1; also elsewhere on the board
POT_LEVEL: C_flt4.1, R_flt4.2, R_pd4.1; also elsewhere on the board
POT_RATE: C_flt3.1, R_flt3.2, R_pd3.1; also elsewhere on the board
TM1637_CLK: J_disp1.1; also elsewhere on the board
TM1637_DIO: J_disp1.2, R_dio1.2; also elsewhere on the board

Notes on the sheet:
CLOCK / V-OCT MODE SWITCH SPDT toggle (Dailywell 2MS1T1B1M2QES) Common (pad 2) -> GND; pad 1 -> MODE_SW -> D8 (pin 9), read INPUT_PULLUP Selects Clock/tempo vs V/oct pitch, and the Rate pot's role
Output Jacks (mono): OUT1, OUT2, CV OUT, GATE OUT (plain, unswitched)
Input Jacks (mono): CV A, CV B, CLK / V-OCT, GATE IN Switched-T type - tip normalled to GND when unpatched.
Pot A
Rotary encoder - 100nF to GND on A/B/SW MCU internal pull-ups enabled in firmware (~4ms RC with ~40k pull-up) Encoder + display GPIO connect directly to Daisy Seed digital pins
TM1637 Display Module (4-pin connector) Pinout: 1=CLK, 2=DIO, 3=GND, 4=+5V. Powered from +5V; R_dio1 (10k) pulls DIO to +3V3. CLK has no pull-up. Firmware requires ~50us bus bit timing - 5us will not latch.
USER INTERFACE Potentiometers | Rotary Encoder | Mode Switch | TM1637 Display Module
Potentiometers with ADC RC Filters ADC RC filter: R_flt (1k) + C_flt (100nF) = 1.59kHz R_pd1-4 (100k) to GND: defines 0V if a wiper opens. 100k (was 10k) - the lighter load recovers ~8% of ADC range.
Pot B
Pot 3 - Rate Dual role: tempo trim in Clock mode, bipolar +/-1 octave fine tune in V/oct mode.
Pot 4 - Tone (Lo-Fi macro)
J_clk1 is dual function: Clock/tempo OR V/oct pitch, per the mode switch. Panel silk: CLK / V-OCT.
